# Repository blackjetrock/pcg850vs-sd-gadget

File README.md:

# pcg850vs-sd-gadget
Gadget for the PC-G850VS family of pocket computers

This gadget:

1. Reads SD card files into memory and then sends them to the PCG850VS
2. Captures data from the PCG850VS and allows it to be written to the SD card
3. Can scope the PIO mod eoutputs of the PC-G850VS

The PCB uses a blue pill as a processor, and an SD card module for the SD card functions. An OLED display allows operatin away from a computer.

Limitations:

The data sent or received is stored in the RAM of the blue pill, so no files greater than the available RAM can be sent or received. 
The SIO protocol has handshaking so this could be used to pause data from the PC-G850VS to the gadget when writing to the SD card. Reading from the card 
could be done without a problem as data is sent once it is read.

An ARM chip with more RAM could be fitted to the blue pill, this is more involved as it requires desoldering the QFP and putting a new one on.

An issue with early code meant that the SD card may not initialise properly. A code fix for this has bee pushed to the repository.

File Tags
---------

If the gadget detects a tag of '@file' (case sensitive) in the file that it has read from the G850 then it usd the filename specified after the tag
(delimited with a space) as the name to use if the file is written to the SD card. If the file tag does not exist then the gadget uses unique
filenames of the form PCGnnnn.DAT where nnnn is chosen to be the next unused value on the SD card.

Circuit
-------

The circuit uses a blue pill to do the processing. The PC-G850VS 11 pin interface is protected by series resistors. Power can come from either the blue pill or the PC-G850VS. If powered by the PC-G850VS short JP1. If you power the gadget from the blue pill when this is shorted then the 5V will be sent into the 5V of the 11 pin interface. I'm not sure what this will d, but it's probably not good.
There's an OLED display that is used to display menus. It is an I2C device. The SD card is held in a catalex SD card module, these are common on ebay.
Three keyswitches are used to control the menu system. As well as the OLED menus there are some commands that can be sent over the USB to serial connection. This needs a USB to serial adapter on J2.

The circuit involving Q1 is an inverter that should allow the UART functionality of the ARM processor to decode the serial data from the PC-G850VS. The current sketch does not use this but rather decodes the data stream using firmware.

For programming I use a STLINK V2 clone from ebay connected to the programming connector of the blue pill.

Construction Notes
==================

Components are fitted as shown on the schematic, apart from a few noted here:

The SD card reader module should be powered from 5V, not 3V3. The PCBs all have a 3V3 supply wired to the module. I have found that some modules will work with a 3V3 supply, but some won't. Cutting the track to the power pin of the module and running  wire from 3V3 to the supply pin of the module fixes the problem.

R14, Q1 and R15 are a hardware level shifter that takes the transmitted data (TX) from the PC-G850VS and sends it to the hardware USART on the blue pill. I don't use this at the moment as the code can decode the serial data. These components can be omitted or fitted. The sketch will have to be adjusted if you want to use the hardware USART.

J7 is a power jumper. If it is shorted then power comes from the PC-G850VS. If open then the blue pill can power the circuit (useful if programming the blue pill).
R4 and R5 are power connections and should be 0R links or wire links.

The blue pill, display and SD card reader can either be soldered to the PCB or fitted in sockets. If soldered then th eprofile is much lower but obviously these parts are harder to remve if you need to.

The SD card reader comes with a right angle type connector, for fitting on the PCB I desolder the connector it comes with and fit a straight connector.

I use a straight pin header for J1 and solder it on the top of the board. This is because straight headers are cheaper and they also lead to a lower profile once fitted.

OLED displays come in two pinouts, with reversed power connections. There's two connectors for the OLED display, one for each pinout. Make sure the OLED display is connected to the correct pinout connector.

I use an ST-LINKV2 from ebay for programming the blue pill. Any method of getting the sketch on to the blue pill should be fine.

Code
----

The menu structure that the code uses varies with the version of code that is running and th efunctions that are added to the code.
The menu option names have been elaborated from th ebasic names given in the instruction sheet, but it should be possible to work out 
which option does what.

Supported Devices
-----------------

The gadget has been used on the:
PC-G850VS
PC-G850

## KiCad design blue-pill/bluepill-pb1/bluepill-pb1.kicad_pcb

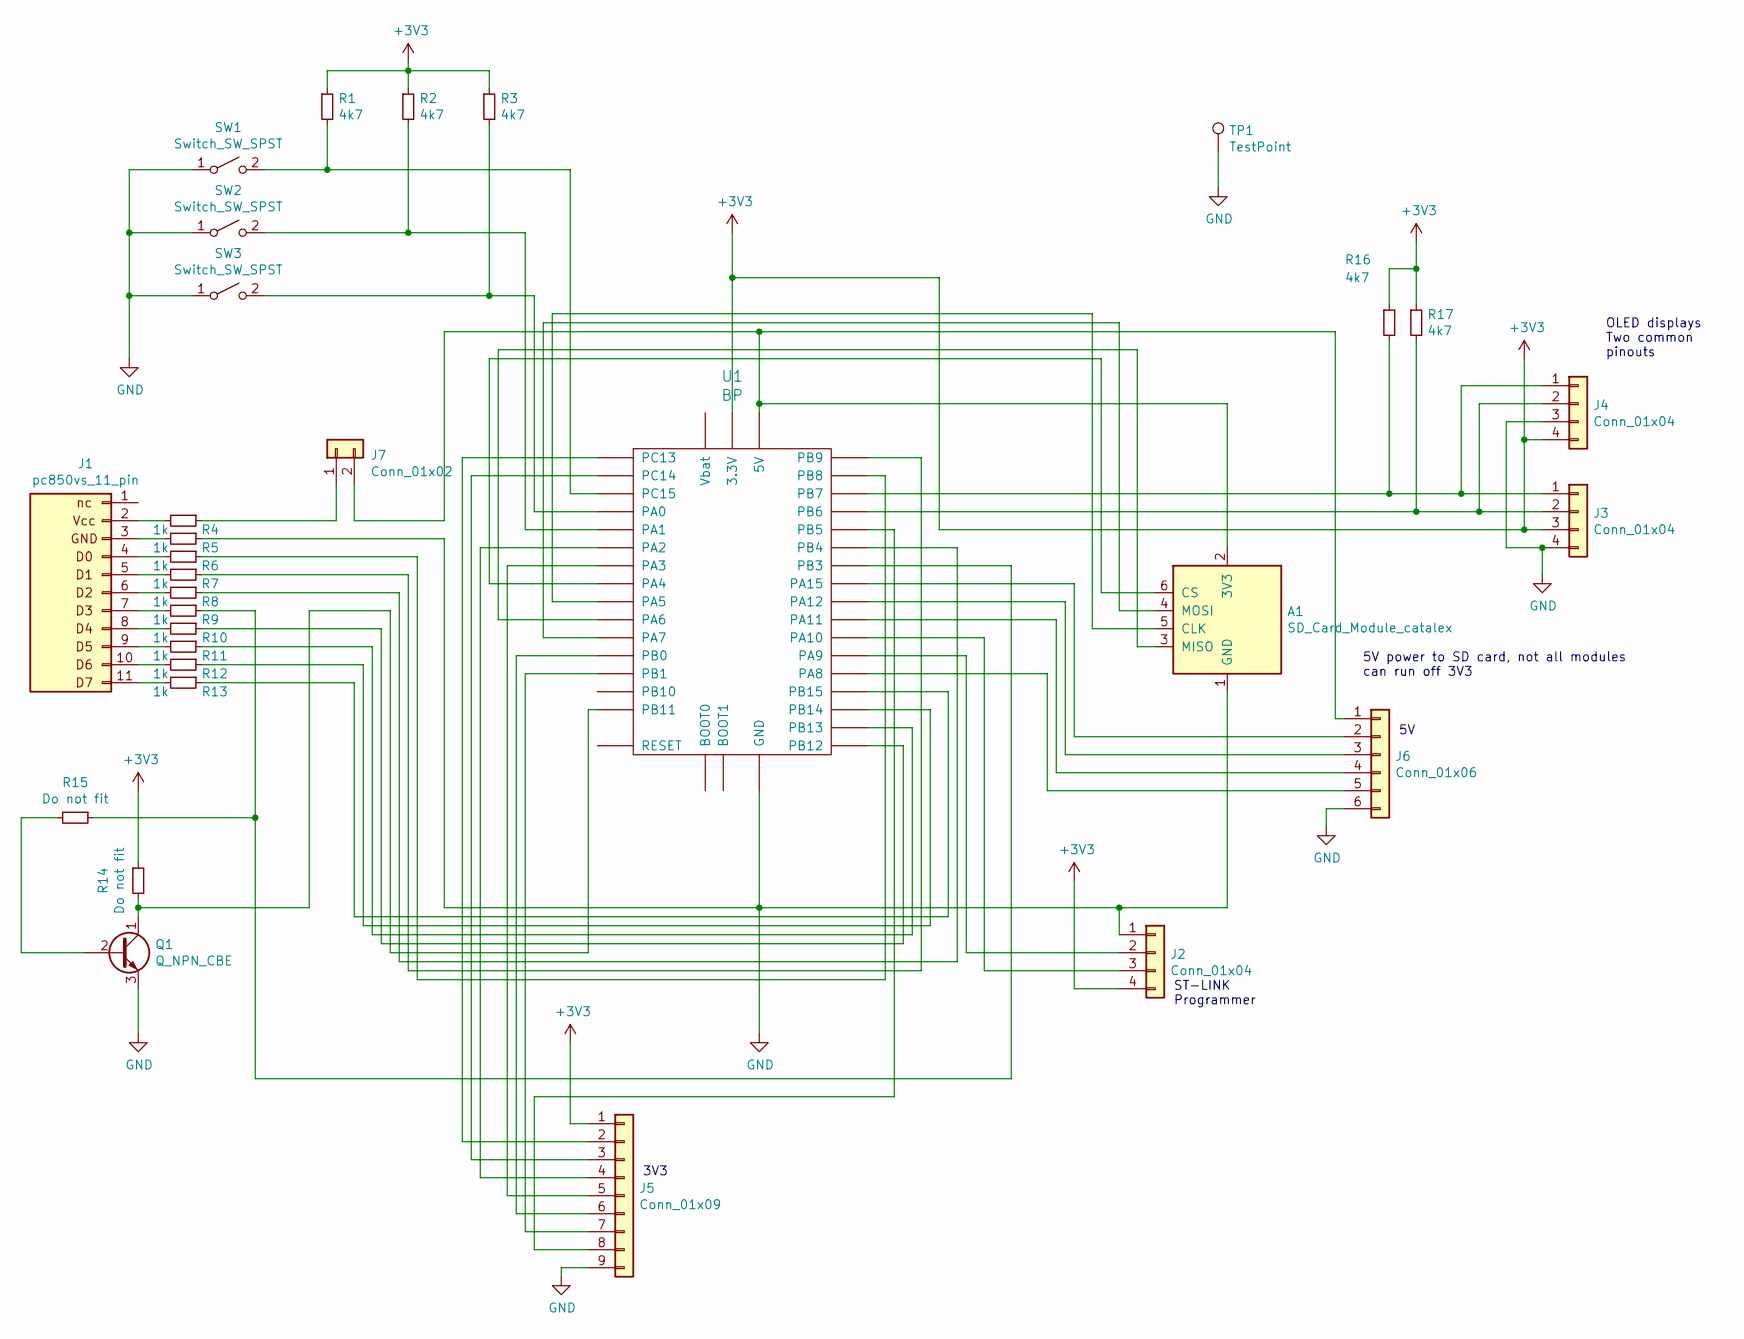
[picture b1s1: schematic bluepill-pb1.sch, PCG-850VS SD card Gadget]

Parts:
A1: SD_Card_Module_catalex; SD_Card_Module
J1: pc850vs_11_pin; PinHeader_1x11_P2.54mm_Vertical
J2, J3, J4: Conn_01x04; PinHeader_1x04_P2.54mm_Vertical
J5: Conn_01x09; PinHeader_1x09_P2.54mm_Vertical
J6: Conn_01x06; PinHeader_1x06_P2.54mm_Vertical
J7: Conn_01x02; PinHeader_1x02_P2.54mm_Vertical
Q1: Q_NPN_CBE; TO92_vert
R1, R2, R3, R16, R17: 4k7; R_Axial_DIN0207_L6.3mm_D2.5mm_P7.62mm_Horizontal
R4, R5, R6, R7, R8, R9, R10, R11, R12, R13: 1k; R_Axial_DIN0207_L6.3mm_D2.5mm_P7.62mm_Horizontal
R14, R15: Do not fit; R_Axial_DIN0207_L6.3mm_D2.5mm_P7.62mm_Horizontal
SW1, SW2, SW3: Switch_SW_SPST; SW_PUSH-12mm
TP1: TestPoint; TestPoint_Loop_D2.60mm_Drill0.9mm_Beaded
U1: BP; BLUEPILL

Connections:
+3V3: J2.4, J3.3, J4.4, J5.1, R1.1, R2.1, R3.1, R14.1, R16.1, R17.1, U1.3V3 (3.3V)
GND: A1.1 (GND), J2.1, J3.4, J4.3, J5.9, J6.6, Q1.3 (E), R5.1, SW1.1 (A), SW2.1 (A), SW3.1 (A), TP1.1, U1.G (GND)
unnamed: A1.2 (3V3), J6.1, J7.2, U1.5V
unnamed: A1.3 (MISO), U1.PA6
unnamed: A1.4 (MOSI), U1.PA7
unnamed: A1.5 (CLK), U1.PA5
unnamed: A1.6 (CS), U1.PA4
unnamed: J1.2 (+5V), R4.2
unnamed: J1.3 (GND), R5.2
unnamed: J1.4 (D0), R6.2
unnamed: J1.5 (D1), R7.2
unnamed: J1.6 (D2), R8.2
unnamed: J1.7 (D3), R9.2
unnamed: J1.8 (D4), R10.2
unnamed: J1.9 (D5), R11.2
unnamed: J1.10 (D6), R12.2
unnamed: J1.11 (D7), R13.2
unnamed: J2.2, U1.PA9
unnamed: J2.3, U1.PA10
unnamed: J3.1, J4.1, R16.2, U1.PB7
unnamed: J3.2, J4.2, R17.2, U1.PB6
unnamed: J5.2, U1.PC13
unnamed: J5.3, U1.PC14
unnamed: J5.4, U1.PA2
unnamed: J5.5, U1.PA3
unnamed: J5.6, U1.PB0
unnamed: J5.7, U1.PB1
unnamed: J5.8, U1.PB5
unnamed: J6.2, U1.PA15
unnamed: J6.3, U1.PA12
unnamed: J6.4, U1.PA11
unnamed: J6.5, U1.PA8
unnamed: J7.1, R4.1
unnamed: Q1.1 (C), R14.2, U1.PB11
unnamed: Q1.2 (B), R15.2
unnamed: R1.2, SW1.2 (B), U1.PC15
unnamed: R2.2, SW2.2 (B), U1.PA1
unnamed: R3.2, SW3.2 (B), U1.PA0
unnamed: R6.1, U1.PB8
unnamed: R7.1, U1.PB9
unnamed: R8.1, U1.PB4
unnamed: R10.1, U1.PB12
unnamed: R11.1, U1.PB13
unnamed: R12.1, U1.PB14
unnamed: R13.1, U1.PB15
unnamed: R9.1, R15.1, U1.PB3

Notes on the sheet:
ST-LINK Programmer
OLED displays Two common pinouts
3V3
5V power to SD card, not all modules can run off 3V3

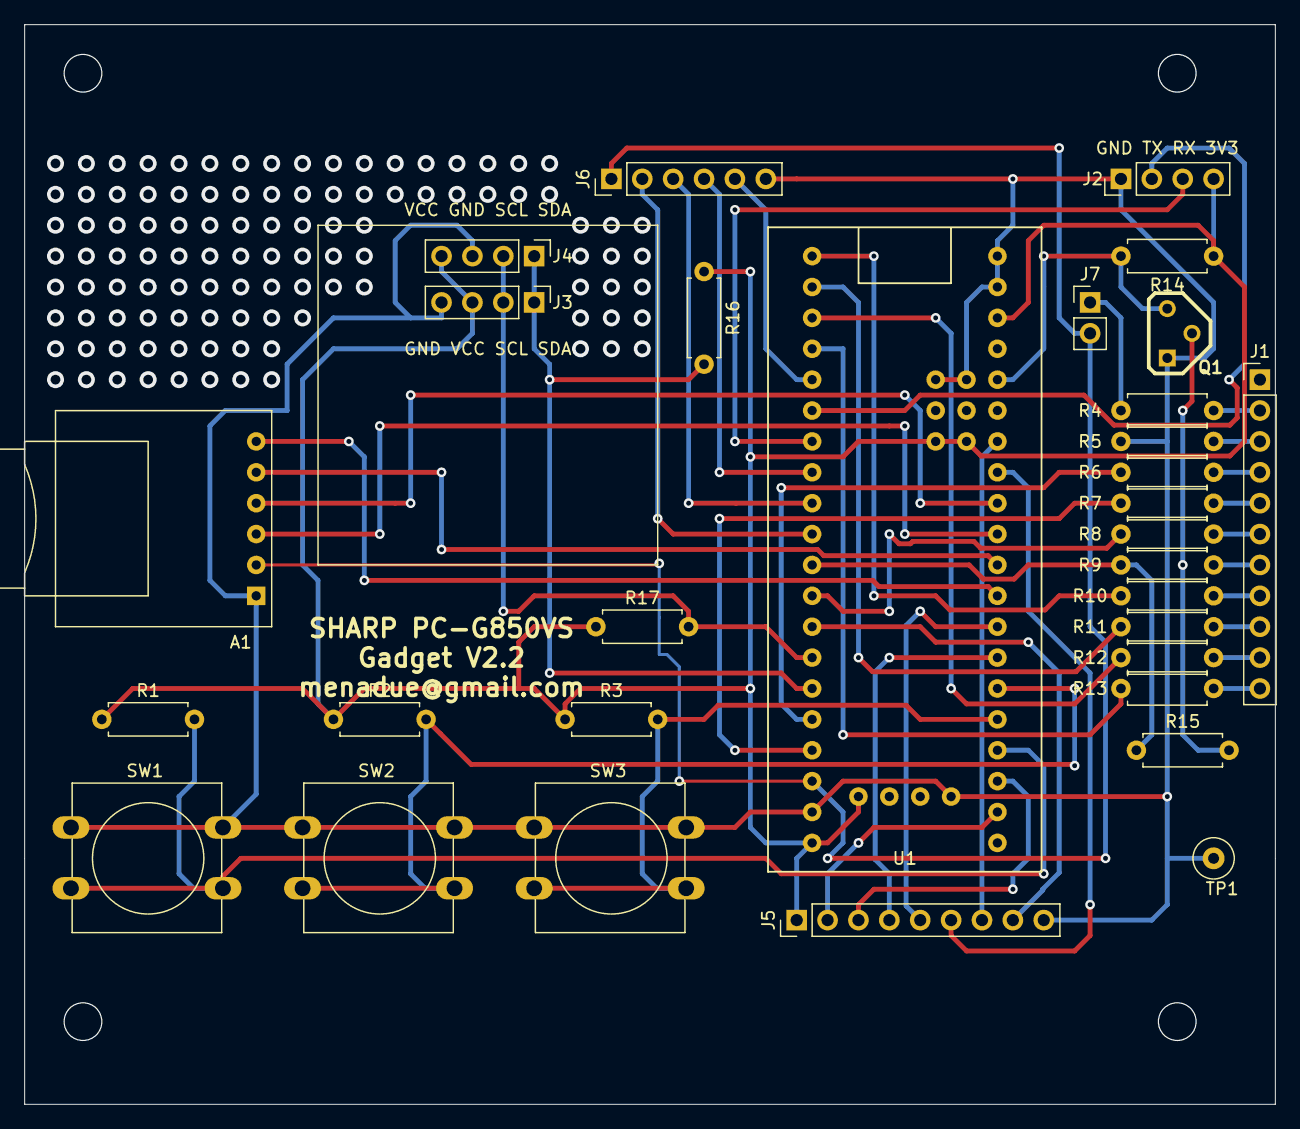
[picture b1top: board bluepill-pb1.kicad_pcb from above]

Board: 2 copper layers, 102.9 x 88.8 mm, 31 parts (0 on the bottom side), 46 nets.

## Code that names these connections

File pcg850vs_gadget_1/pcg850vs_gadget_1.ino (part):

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const int chipSelect = 4;

// Pins for Sharp 11 pin interface data lines
const int IFD0Pin  = PB8;
const int IFD1Pin  = PB9;
const int IFD2Pin  = PB4;
const int IFD3Pin  = PB3;
const int IFD4Pin  = PB12;
const int IFD5Pin  = PB13;
const int IFD6Pin  = PB14;
const int IFD7Pin  = PB15;

// SIO pins
const int SIORTSPin = IFD0Pin;
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const int SIOEX2Pin  = IFD7Pin;

// Debug outputs
const int statPin   = PC13;
const int dataPin   = PC14;


#define NIF 8
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// STM32F103C8 has only 20k of SRAM
//const int MAX_BYTES = 10000;
const int MAX_BYTES = 10000; 
const int button1Pin = PA0;
const int button2Pin = PA1;
const int button3Pin = PC15;

typedef unsigned char BYTE;

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//
////////////////////////////////////////////////////////////////////////////////////////////////////

//HardwareSerial Serial1(PA10, PA9);
HardwareSerial Serial2(PB11, PB10);

void setup() {

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  // until we decide to do some work over the interface
  set_if_inputs();

  pinMode(PA0, INPUT);
  pinMode(PA1, INPUT);
  pinMode(PA2, INPUT);

  // Set SD card CS GPIO to be an output
  digitalWrite(PA4, LOW);
  pinMode(PA4, OUTPUT);
  
  digitalWrite(PA4, LOW);
  pinMode(PA4, OUTPUT);
  
  pinMode(statPin, OUTPUT);
  pinMode(dataPin, OUTPUT);
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
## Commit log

2020-10-09 Created files for public repository
2020-11-07 Update README.md
    Added SD module power supply problem to construction notes.
2021-01-21 Added samples
2021-05-31 Added instruction sheet
2021-06-03 Added information file
2021-07-09 Added component values
2021-10-05 Fix to issue #2
    The SD card would sometimes not initialise. A possible fix to this is in this
    commit.
    By putting a finger on various terminals I found that the CS pin of the SD card adapter
    could stop initialisation of the card if it was held high. Holding it low with a high-ish
    resistance allowed the SD card to initialise every time. With the theory that the CS line
    was activating before or during the SD card initialisation and messing it up, holding it low with a resistor
2021-10-07 Applied SD module patch by blackjetrock
2021-10-07 Refined button event trigger
2021-10-07 Implemented the first cut of file name annotation
2021-10-08 Align the formatting style; added comments
2021-11-04 Fixed the buffer offset issue after SIO made active
2022-08-21 Merged Steve Harvey's changes. V2.0
2022-08-22 V2.1: Tidied version string and menus
2022-08-27 Improved comments
2022-08-27 Added a mode that can receive SSIO (CE-126) data. This means that you can do LPRINT or LLIST and get that data sent to the buffer. Temporarily commented out as the extra menu item fills the screen an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
2022-08-28 Added 'Send File' menu option. This sends the file data directly from an SD card file so has no buffer involved and hence no length limit. Re-arranged menus so they always fit on a screen.
2022-08-30 Re-arranged menus a bit to make room for new SSIO and PCU menus.
    Fixes:
    1. Menus can now scroll like the file name display
    2. SSIO menu added. This works with the PCG850VS when it has done an OPEN("LPRT:") and then issues
    an LPRINT, LFILES or LLIST command. The output is sent to the gadget.
    SSIO mode is not on th eother Sharp pocket computers, they use the PCU protocol below
    3. Added a PCU (Printer Control Unit) protocol which is designed to appear as a CE-126 printer/cassette
2022-08-31 Added a status line at the top of the OLED screen. This shows the current number of bytes in the buffer at the left and the current transfer protocol at the right. This is in preparation for the diff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
2022-09-28 Added PCB V2.2, which fixes the wire needed on V2.1
